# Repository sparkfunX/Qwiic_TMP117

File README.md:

SparkX Qwiic TMP117
========================================

[*High Precision Temperature Sensor - TMP117 (Qwiic) (SPX-15413)*](https://www.sparkfun.com/products/15413)

The TMP117 is a high precision temperature Sensor with accuracy of up to +/-0.1 degrees celsius and an operating temperature range of -55°C to +150°C. It is NIST traceable and verified with equipment that is calibrated to ISO/IEC 17025 accredited standards. It has a very low power consumption with a supply range of 1.8V to 5.5V. 

The TMP117 address can be changed with an external jumper to 4 different addresses. There are 4 different conversion modes that it can read from, with continuous conversion, shutdown, and one shot conversion. There is also digital offset for system correction, programmable temperature limits, General-Purpose EEPROM, and selectable averaging. 

Repository Contents
-------------------

* **/Documents** - Data sheet for the TMP117
* **/Hardware** - Eagle design files (.brd, .sch)
* **/Production** - Production panel files (.brd) within the Production folder

License Information
-------------------

This product is _**open source**_! 

Please review the LICENSE.md file for license information. 

If you have any questions or concerns on licensing, please contact technical support on our [SparkFun forums](https://forum.sparkfun.com/viewforum.php?f=152).

Distributed as-is; no warranty is given.

- Your friends at SparkFun.

_<COLLABORATION CREDIT>_

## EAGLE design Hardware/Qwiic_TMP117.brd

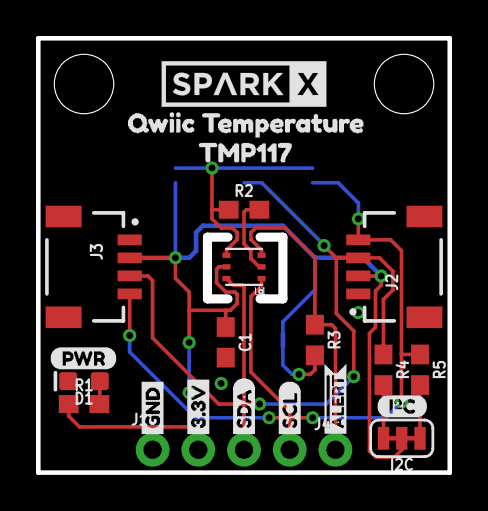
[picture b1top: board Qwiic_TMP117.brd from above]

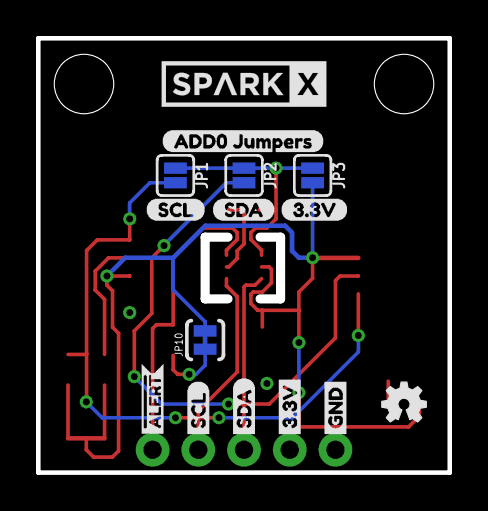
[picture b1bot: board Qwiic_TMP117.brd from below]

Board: 2 copper layers, 22.6 x 23.9 mm, 41 parts (15 on the bottom side), 10 nets.

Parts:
C1: 0.1uF; 0603
D1: RED; LED-0603
FRAME1: FRAME-LETTER; CREATIVE_COMMONS
I2C: SMT-JUMPER_3_2-NC_TRACE_SILK
J1: PTH; 1X04_NO_SILK
J2, J3: JST04_1MM_RA
J4: 1X01_NO_SILK
JP1, JP2, JP3: SMT-JUMPER_2_NO_SILK
JP8, JP9: STAND-OFF
JP10: INT; PAD-JUMPER-2-NC_BY_TRACE_YES_SILK
LOGO1: OSHW-LOGOMINI; OSHW-LOGO-MINI
R1: 1k; 0603
R2, R3: 10k; 0603
R4, R5: 2.2k; 0603
U1: TMP117
U$1: ADD0_JUMPERS0
U$2, U$17: SPARKX-MEDIUM
U$4: TMP1171
U$5: 3#3V2
U$6: QWIIC_TEMPERATURE2
U$7, U$20: #ALERT0
U$8: SCL1
U$9, U$11: 3#3V5
U$10, U$12: GND4
U$13, U$16: SCL7
U$14, U$15: SDA6
U$18: SDA0
U$19: I_SUPER2_C-()-03
U$21: PWR-()-03

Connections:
3.3V: C1.1, I2C.2, J1.2, J2.2, J3.2, JP3.2, JP10.2, R1.1, U1.5
!ALERT: J4.1, R3.1, U1.3
ADD0: JP1.1, JP2.1, JP3.1, R2.1, U1.4
GND: C1.2, D1.C, J1.1, J2.1, J3.1, R2.2, U1.2
unnamed: D1.A, R1.2
unnamed: I2C.1, R5.2
unnamed: I2C.3, R4.2
unnamed: JP10.1, R3.2
SCL: J1.4, J2.4, J3.4, JP1.2, R5.1, U1.1
SDA: J1.3, J2.3, J3.3, JP2.2, R4.1, U1.6

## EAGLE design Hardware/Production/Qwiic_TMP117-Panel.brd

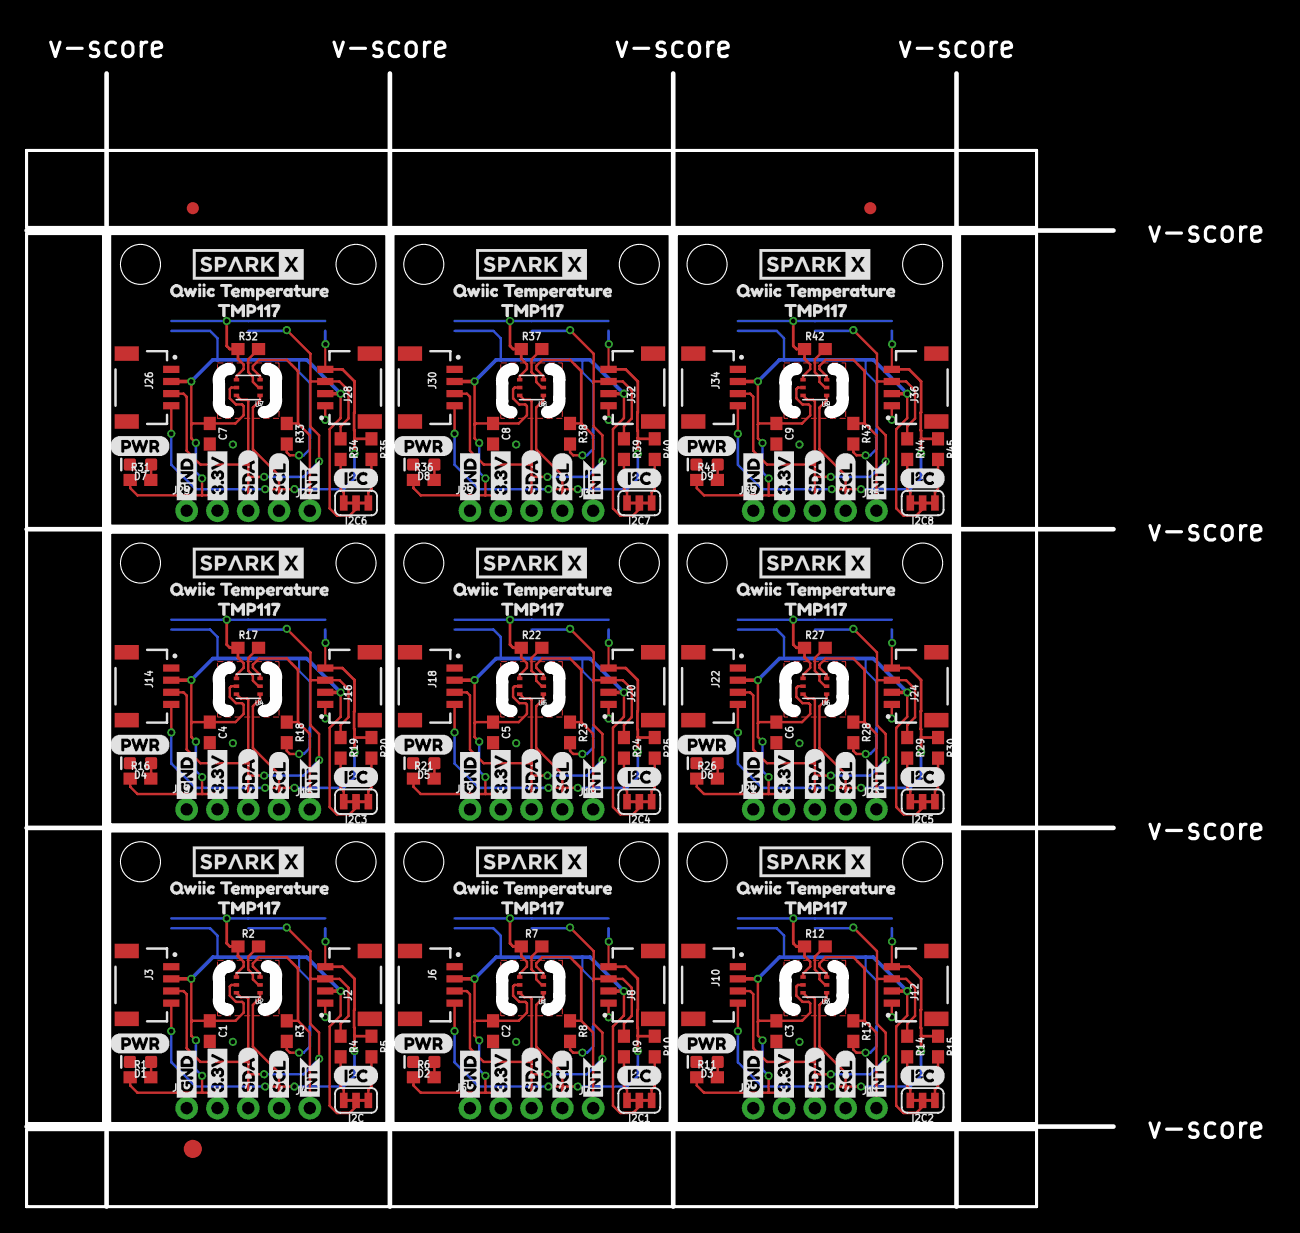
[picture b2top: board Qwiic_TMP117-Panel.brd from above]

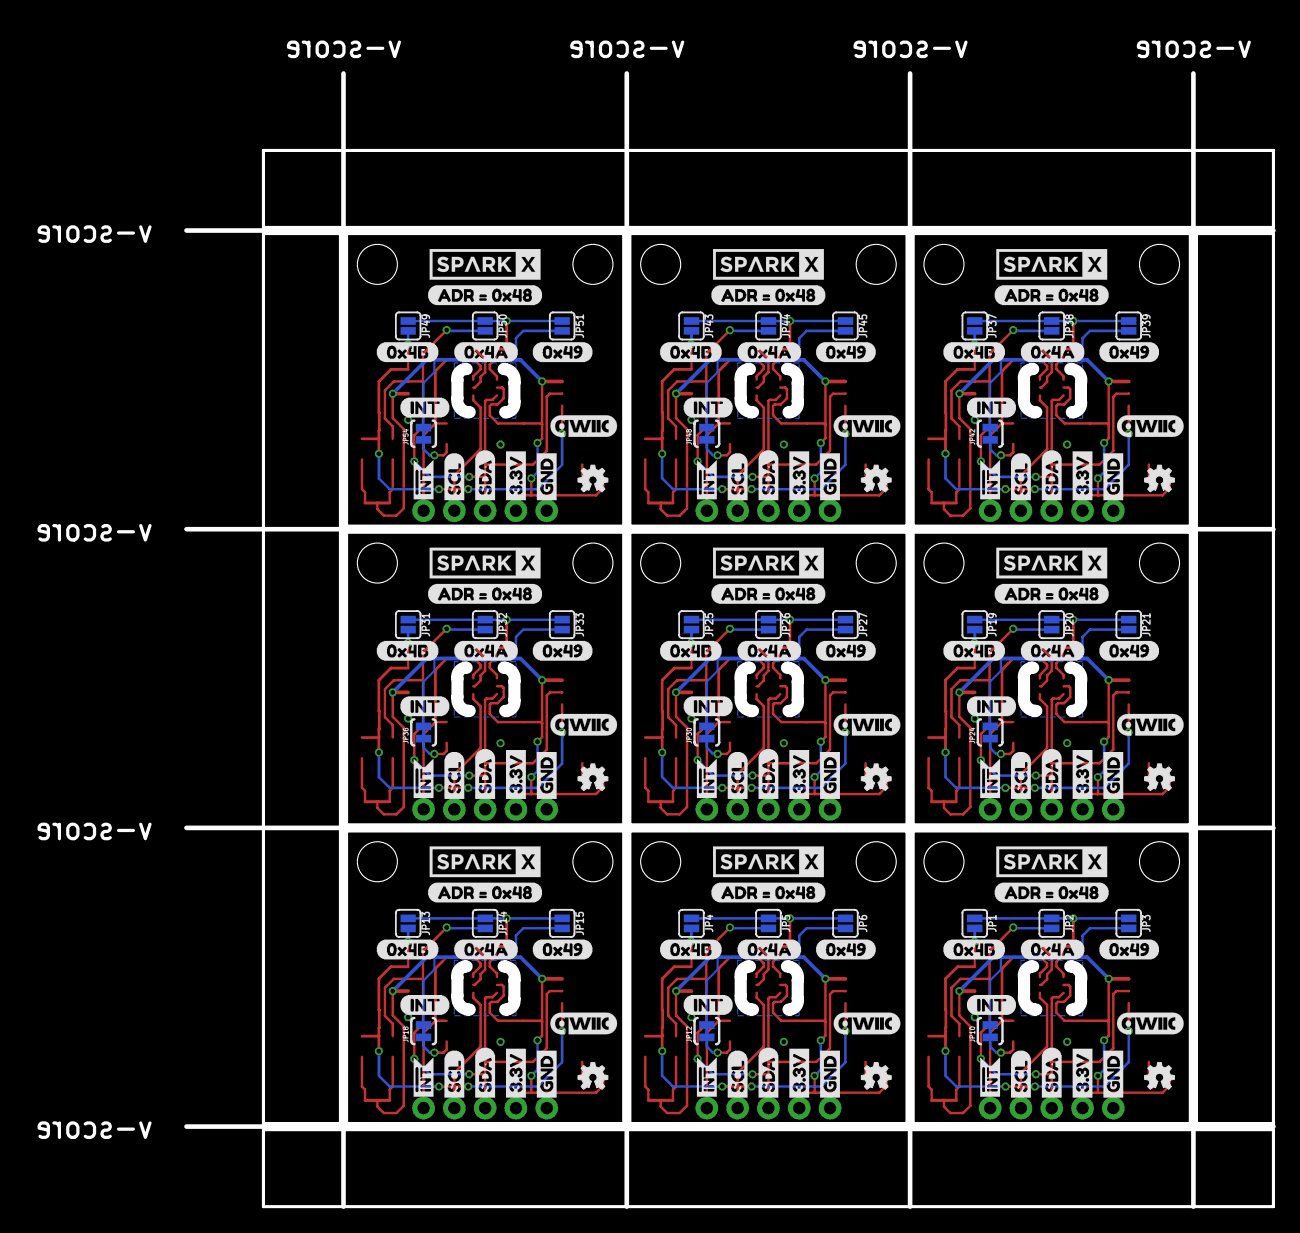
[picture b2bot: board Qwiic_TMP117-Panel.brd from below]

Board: 2 copper layers, 102.2 x 96.7 mm, 381 parts (153 on the bottom side), 90 nets.

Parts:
C1, C2, C3, C4, C5, C6, C7, C8, C9: 0.1uF; 0603
D1, D2, D3, D4, D5, D6, D7, D8, D9: RED; LED-0603
E$1, E$2: FIDUCIAL-1X2
E$3: FIDUCIAL-1.5X3
I2C, I2C1, I2C2, I2C3, I2C4, I2C5, I2C6, I2C7, I2C8: SMT-JUMPER_3_2-NC_TRACE_SILK
J1, J5, J9, J13, J17, J21, J25, J29, J33: PTH; 1X04_NO_SILK
J2, J3, J6, J8, J10, J12, J14, J16, J18, J20, J22, J24, J26, J28, J30, J32, J34, J36: JST04_1MM_RA
J4, J7, J11, J15, J19, J23, J27, J31, J35: 1X01_NO_SILK
JP1, JP2, JP3, JP4, JP5, JP6, JP13, JP14, JP15, JP19, JP20, JP21, JP25, JP26, JP27, JP31, JP32, JP33, JP37, JP38, JP39, JP43, JP44, JP45, JP49, JP50, JP51: SMT-JUMPER_2_NO_SILK
JP7, JP8, JP9, JP11, JP16, JP17, JP22, JP23, JP28, JP29, JP34, JP35, JP40, JP41, JP46, JP47, JP52, JP53: STAND-OFF
JP10, JP12, JP18, JP24, JP30, JP36, JP42, JP48, JP54: INT; PAD-JUMPER-2-NC_BY_TRACE_YES_SILK
LOGO1, LOGO2, LOGO3, LOGO4, LOGO5, LOGO6, LOGO7, LOGO8, LOGO9: OSHW-LOGOMINI; OSHW-LOGO-MINI
R1, R6, R11, R16, R21, R26, R31, R36, R41: 1k; 0603
R2, R3, R7, R8, R12, R13, R17, R18, R22, R23, R27, R28, R32, R33, R37, R38, R42, R43: 10k; 0603
R4, R5, R9, R10, R14, R15, R19, R20, R24, R25, R29, R30, R34, R35, R39, R40, R44, R45: 2.2k; 0603
U1, U2, U3, U4, U5, U6, U7, U8, U9: TMP117
U$1, U$40, U$62, U$84, U$106, U$128, U$150, U$172, U$194: 0X4B1
U$2, U$17, U$25, U$26, U$47, U$48, U$69, U$70, U$91, U$92, U$113, U$114, U$135, U$136, U$157, U$158, U$179, U$180: SPARKX-MEDIUM
U$3, U$11, U$27, U$30, U$49, U$52, U$71, U$74, U$93, U$96, U$115, U$118, U$137, U$140, U$159, U$162, U$181, U$184: INT#-[<-04
U$4, U$16, U$45, U$67, U$89, U$111, U$133, U$155, U$177: TMP1171
U$5, U$41, U$63, U$85, U$107, U$129, U$151, U$173, U$195: 0X4A0
U$6, U$24, U$46, U$68, U$90, U$112, U$134, U$156, U$178: QWIIC_TEMPERATURE2
U$7, U$28, U$50, U$72, U$94, U$116, U$138, U$160, U$182: INT-()-04
U$8, U$42, U$64, U$86, U$108, U$130, U$152, U$174, U$196: 0X493
U$9, U$12, U$29, U$37, U$51, U$59, U$73, U$81, U$95, U$103, U$117, U$125, U$139, U$147, U$161, U$169, U$183, U$191: SCL-[)
U$10, U$23, U$35, U$36, U$57, U$58, U$79, U$80, U$101, U$102, U$123, U$124, U$145, U$146, U$167, U$168, U$189, U$190: GND-04
U$13, U$14, U$38, U$39, U$60, U$61, U$82, U$83, U$104, U$105, U$126, U$127, U$148, U$149, U$170, U$171, U$192, U$193: SDA-[)
U$15, U$44, U$66, U$88, U$110, U$132, U$154, U$176, U$198: QWIIC_5.5MM
U$18, U$43, U$65, U$87, U$109, U$131, U$153, U$175, U$197: ADR_#_0X484
U$19, U$22, U$33, U$34, U$55, U$56, U$77, U$78, U$99, U$100, U$121, U$122, U$143, U$144, U$165, U$166, U$187, U$188: 3.3V
U$20, U$31, U$53, U$75, U$97, U$119, U$141, U$163, U$185: PWR-()-04
U$21, U$32, U$54, U$76, U$98, U$120, U$142, U$164, U$186: I_SUPER2_C-()-04

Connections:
3.3V: C1.1, I2C.2, J1.2, J2.2, J3.2, JP3.2, JP10.2, R1.1, U2.5
3.3V1: C2.1, I2C1.2, J5.2, J6.2, J8.2, JP6.2, JP12.2, R6.1, U1.5
3.3V2: C3.1, I2C2.2, J9.2, J10.2, J12.2, JP15.2, JP18.2, R11.1, U3.5
3.3V3: C4.1, I2C3.2, J13.2, J14.2, J16.2, JP21.2, JP24.2, R16.1, U4.5
3.3V4: C5.1, I2C4.2, J17.2, J18.2, J20.2, JP27.2, JP30.2, R21.1, U5.5
3.3V5: C6.1, I2C5.2, J21.2, J22.2, J24.2, JP33.2, JP36.2, R26.1, U6.5
3.3V6: C7.1, I2C6.2, J25.2, J26.2, J28.2, JP39.2, JP42.2, R31.1, U7.5
3.3V7: C8.1, I2C7.2, J29.2, J30.2, J32.2, JP45.2, JP48.2, R36.1, U8.5
3.3V8: C9.1, I2C8.2, J33.2, J34.2, J36.2, JP51.2, JP54.2, R41.1, U9.5
!INT: J4.1, R3.1, U2.3
!INT1: J7.1, R8.1, U1.3
!INT2: J11.1, R13.1, U3.3
!INT3: J15.1, R18.1, U4.3
!INT4: J19.1, R23.1, U5.3
!INT5: J23.1, R28.1, U6.3
!INT6: J27.1, R33.1, U7.3
!INT7: J31.1, R38.1, U8.3
!INT8: J35.1, R43.1, U9.3
ADD0: JP1.1, JP2.1, JP3.1, R2.1, U2.4
ADD1: JP4.1, JP5.1, JP6.1, R7.1, U1.4
ADD2: JP13.1, JP14.1, JP15.1, R12.1, U3.4
ADD3: JP19.1, JP20.1, JP21.1, R17.1, U4.4
ADD4: JP25.1, JP26.1, JP27.1, R22.1, U5.4
ADD5: JP31.1, JP32.1, JP33.1, R27.1, U6.4
ADD6: JP37.1, JP38.1, JP39.1, R32.1, U7.4
ADD7: JP43.1, JP44.1, JP45.1, R37.1, U8.4
ADD8: JP49.1, JP50.1, JP51.1, R42.1, U9.4
GND: C1.2, D1.C, J1.1, J2.1, J3.1, R2.2, U2.2
GND1: C2.2, D2.C, J5.1, J6.1, J8.1, R7.2, U1.2
GND2: C3.2, D3.C, J9.1, J10.1, J12.1, R12.2, U3.2
GND3: C4.2, D4.C, J13.1, J14.1, J16.1, R17.2, U4.2
GND4: C5.2, D5.C, J17.1, J18.1, J20.1, R22.2, U5.2
GND5: C6.2, D6.C, J21.1, J22.1, J24.1, R27.2, U6.2
GND6: C7.2, D7.C, J25.1, J26.1, J28.1, R32.2, U7.2
GND7: C8.2, D8.C, J29.1, J30.1, J32.1, R37.2, U8.2
GND8: C9.2, D9.C, J33.1, J34.1, J36.1, R42.2, U9.2
unnamed: D1.A, R1.2
unnamed: I2C.1, R5.2
unnamed: I2C.3, R4.2
unnamed: JP10.1, R3.2
unnamed: D2.A, R6.2
unnamed: I2C1.1, R10.2
unnamed: I2C1.3, R9.2
unnamed: JP12.1, R8.2
unnamed: D3.A, R11.2
unnamed: I2C2.1, R15.2
unnamed: I2C2.3, R14.2
unnamed: JP18.1, R13.2
unnamed: D4.A, R16.2
unnamed: I2C3.1, R20.2
unnamed: I2C3.3, R19.2
unnamed: JP24.1, R18.2
unnamed: D5.A, R21.2
unnamed: I2C4.1, R25.2
unnamed: I2C4.3, R24.2
unnamed: JP30.1, R23.2
unnamed: D6.A, R26.2
unnamed: I2C5.1, R30.2
unnamed: I2C5.3, R29.2
unnamed: JP36.1, R28.2
unnamed: D7.A, R31.2
unnamed: I2C6.1, R35.2
unnamed: I2C6.3, R34.2
unnamed: JP42.1, R33.2
unnamed: D8.A, R36.2
unnamed: I2C7.1, R40.2
unnamed: I2C7.3, R39.2
unnamed: JP48.1, R38.2
unnamed: D9.A, R41.2
unnamed: I2C8.1, R45.2
unnamed: I2C8.3, R44.2
unnamed: JP54.1, R43.2
SCL: J1.4, J2.4, J3.4, JP1.2, R5.1, U2.1
SCL1: J5.4, J6.4, J8.4, JP4.2, R10.1, U1.1
SCL2: J9.4, J10.4, J12.4, JP13.2, R15.1, U3.1
SCL3: J13.4, J14.4, J16.4, JP19.2, R20.1, U4.1
SCL4: J17.4, J18.4, J20.4, JP25.2, R25.1, U5.1
SCL5: J21.4, J22.4, J24.4, JP31.2, R30.1, U6.1
SCL6: J25.4, J26.4, J28.4, JP37.2, R35.1, U7.1
SCL7: J29.4, J30.4, J32.4, JP43.2, R40.1, U8.1
SCL8: J33.4, J34.4, J36.4, JP49.2, R45.1, U9.1
SDA: J1.3, J2.3, J3.3, JP2.2, R4.1, U2.6
SDA1: J5.3, J6.3, J8.3, JP5.2, R9.1, U1.6
SDA2: J9.3, J10.3, J12.3, JP14.2, R14.1, U3.6
SDA3: J13.3, J14.3, J16.3, JP20.2, R19.1, U4.6
SDA4: J17.3, J18.3, J20.3, JP26.2, R24.1, U5.6
SDA5: J21.3, J22.3, J24.3, JP32.2, R29.1, U6.6
SDA6: J25.3, J26.3, J28.3, JP38.2, R34.1, U7.6
SDA7: J29.3, J30.3, J32.3, JP44.2, R39.1, U8.6
SDA8: J33.3, J34.3, J36.3, JP50.2, R44.1, U9.6

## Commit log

2019-04-19 Updated Schematic and Boar
    Fixed the board with the polygon and added a table to the schematic describing the pin addresses for ADD0
2019-04-26 Updated PCB
    Fixed the board to meet the specifications for the data sheet's PCB considerations
2019-04-26 Updated Board
    Fixed wiring and polygons
2019-05-13 Final Design
    Final updated board with the production panelized board and Gerber files
2019-05-13 Updated README File
2019-05-15 Updated PCB
    PCB updated to meet the jlcpcb specs with new milling width
2019-05-21 Updated Library and README File
    Added the library to the file
2019-05-22 Added TMP117_Footpring Library
2019-05-23 Moved Arduino Files to own repo
2019-05-31 Updated Files

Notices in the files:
parts and their libraries:
SparkFun-Capacitors: Licensing: Creative Commons ShareAlike 4.0 International - https://creativecommons.org/licenses/by-sa/4.0
SparkFun-Aesthetics: Released under the Creative Commons Attribution Share-Alike 4.0 License
SparkFun-Aesthetics: https://creativecommons.org/licenses/by-sa/4.0
